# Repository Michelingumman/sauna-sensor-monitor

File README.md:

# 🔥 Sauna Monitoring System with ESP32

A smart monitoring system that tracks temperature and humidity in saunas, detects sessions automatically, and provides real-time visualization through an OLED display and optional web interface.

## 🔍 Overview

This ESP32-based system provides comprehensive monitoring for saunas, automatically detecting when sessions begin and end based on temperature changes. The device displays real-time data on an OLED screen and can optionally connect to Blynk for remote monitoring.

## ✨ Features

### Time Synchronization
- Automatically syncs with NTP servers for accurate time display
- Shows current time in format: `Monday 01-13:00`

### Intelligent Session Detection
- Automatically detects sauna sessions when temperature rises from 20°C to 30°C within 15 minutes
- Tracks session duration and highest temperature
- Detects session end when temperature drops to 30% of peak temperature

### Real-time Monitoring
- Updates temperature and humidity readings every 2 seconds
- Shows current readings with icons
- Sauna Session active indicator

### Connectivity
- Wi-Fi connectivity for time synchronization
- Built-in web server with real-time dashboard
- OTA (Over-the-Air) update capability

## 🛠️ Hardware Requirements

### Components
- **ESP32 Development Board**: Any standard ESP32 board
- **SSD1306 OLED Display**: I2C interface
- **SHT2x Temperature/Humidity Sensor**: I2C interface

### Connections
| Component | ESP32 Pin |
|-----------|-----------|
| OLED SDA  | GPIO 6    |
| OLED SCL  | GPIO 7    |
| SHT2x     | Same I2C bus |
| Power     | 3.3V      |

## 💻 Software Requirements

### Development Environment
- PlatformIO (recommended) or Arduino IDE
- Git (optional, for version control)

### Required Libraries
- Adafruit SSD1306
- Adafruit GFX
- SHT2x library
- AsyncTCP
- ESPAsyncWebServer
- ElegantOTA
- WiFi (built into ESP32 core)

## 📥 Installation & Setup

### 1. Clone or Download the Repository
```bash
git clone https://github.com/yourusername/sauna-sensor-monitor.git
cd sauna-sensor-monitor
```

### 2. Create secrets.h File
Create a file named `secrets.h` in the src directory with the following content:

```cpp
#ifndef SECRETS_H
#define SECRETS_H

#define WIFI_SSID "your_ssid"
#define WIFI_PASS "your_password"

#endif //SECRETS_H
```

> **⚠️ IMPORTANT**: Never commit the secrets.h file to version control. It contains sensitive information. Add it to .gitignore

### 3. Upload to ESP32
Using PlatformIO or Arduino IDE, compile and upload the code to your ESP32 board.

## ⚙️ How It Works

### Startup Sequence
1. ESP32 initializes and connects to WiFi using credentials from secrets.h
2. Synchronizes time with NTP servers and configures for correct timezone
3. Initializes the web server and OTA update capability
4. Begins monitoring temperature and humidity

### Main Operation Loop
- **Time Display**: Updates time at the top of the OLED once per minute
- **Sauna Detection**:
  - Monitors for temperature rise (20°C → 30°C within 15 minutes)
  - When detected, starts session timer and tracks peak temperature
  - Ends session when temperature drops below 30% of peak value
- **Data Visualization**:
  - Updates temperature and humidity readings every 10 seconds
  - Plots temperature as solid line and humidity as dotted line
  - Shows current values with icons

### Web Interface
- Provides a modern, responsive dashboard
- Displays real-time temperature and humidity
- Shows session status and historical data
- Enables OTA firmware updates

## 🔧 Configuration

The project can be configured by modifying the following parameters in main.cpp:

```cpp
// OLED display settings
#define SCREEN_WIDTH 128        // OLED display width
#define SCREEN_HEIGHT 64        // OLED display height
#define OLED_RESET    -1        // Reset pin
#define SCREEN_ADDRESS 0x3C     // I2C address
#define SDA_PIN 6               // SDA pin
#define SCL_PIN 7               // SCL pin

// Timing settings
const unsigned long WIFI_RETRY_INTERVAL = 60000;  // WiFi retry (1 min)
const unsigned long WIFI_CONNECT_TIMEOUT = 10000; // WiFi timeout (10 sec)
```

---

Built with ❤️ for enhanced sauna experiences.

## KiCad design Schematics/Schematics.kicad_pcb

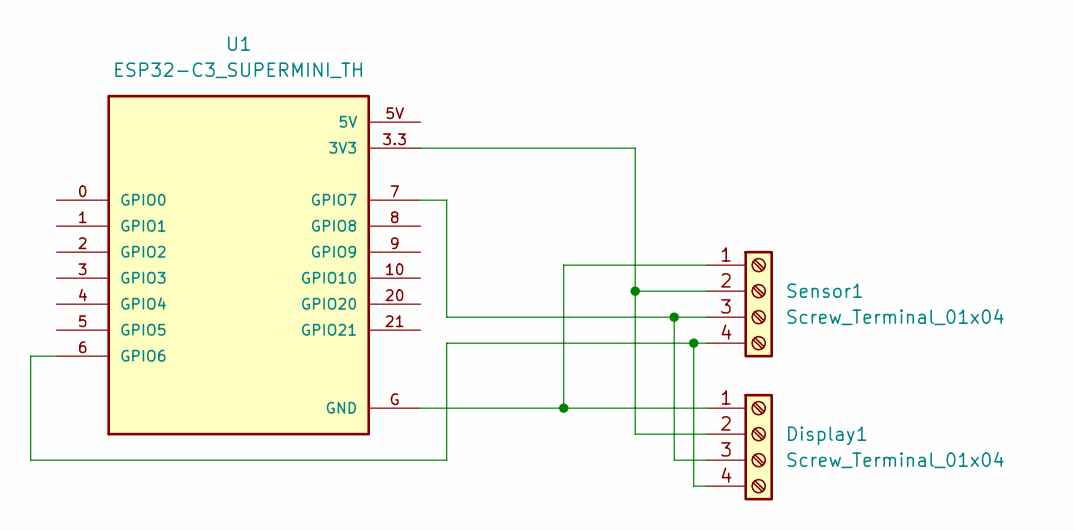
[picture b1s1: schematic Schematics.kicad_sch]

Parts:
Display1: Screw_Terminal_01x04; 128x64OLED
Sensor1: Screw_Terminal_01x04; TerminalBlock_Altech_AK300-4_P5.00mm
U1: ESP32-C3_SUPERMINI_TH; MODULE_ESP32-C3_SUPERMINI

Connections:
unnamed: Display1.1, Sensor1.1, U1.G (GND)
unnamed: Display1.2, Sensor1.2, U1.3.3 (3V3)
unnamed: Display1.3, Sensor1.3, U1.7 (GPIO7)
unnamed: Display1.4, Sensor1.4, U1.6 (GPIO6)

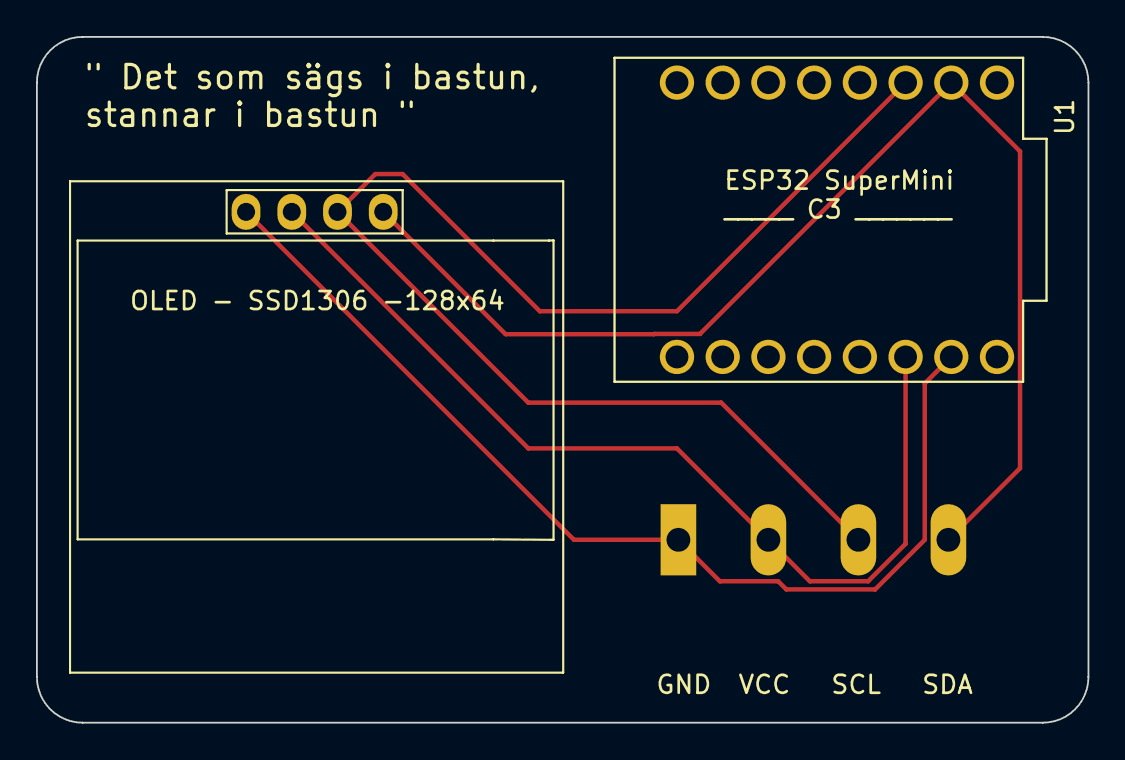
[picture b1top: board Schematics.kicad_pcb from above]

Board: 2 copper layers, 58.4 x 38.1 mm, 3 parts (1 on the bottom side), 4 nets.

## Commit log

2025-02-25 Add initial project structure with configuration and documentation
2025-02-25 Update OLED display I2C address to 0x70
2025-02-26 Add GPIO Viewer integration and update serial monitor settings
2025-03-01 updated logic for sauna state and displaying temp/hum,
    not testeed with display irl
2025-03-03 Refactor loop logic to improve time display and sensor data logging
2025-03-09 Working OTA and display implementation
2025-03-09 Fully functional exepct for json data via web not displaing on IP adress
2025-03-09 importing KiCad Files
2025-03-09 removing unused test file
2025-03-09 Enhanced ReadMe
